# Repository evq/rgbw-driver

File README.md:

# RGBW LED Driver

A four channel LED driver board, designed for use with the Maple Mini
and other generic STM32F103 boards available on ebay and aliexpress. Shield
format, expecting PWM input from pins 8-11.

Shared on [OSH Park.](https://oshpark.com/shared_projects/hxdjCOfY)

## BOM

| Name           | Part                        |
|----------------|-----------------------------|
| Q1, Q2, Q3, Q4 | STN4NF03L N-Channel SOT-223 |
| R1, R2, R3, R4 | 0805 1M resistor            |
| R5, R6, R7, R8 | 0805 1k resistor            |

## Design notes
Polygon pours and thermal vias to help with any heat management issues.
Tested, board was produced by OSH Park. Designed to use the STN4NF03L
SOT-223 SMT N Channel MOSFET, but others could be substituted appropriately.

Designed to allow substitution with
right angle female pin header as surface mount to allow for mounting
of larger heatsink on the back. "LM2596 style" heatsinks (50mm x 25mm x 10mm) work
great.

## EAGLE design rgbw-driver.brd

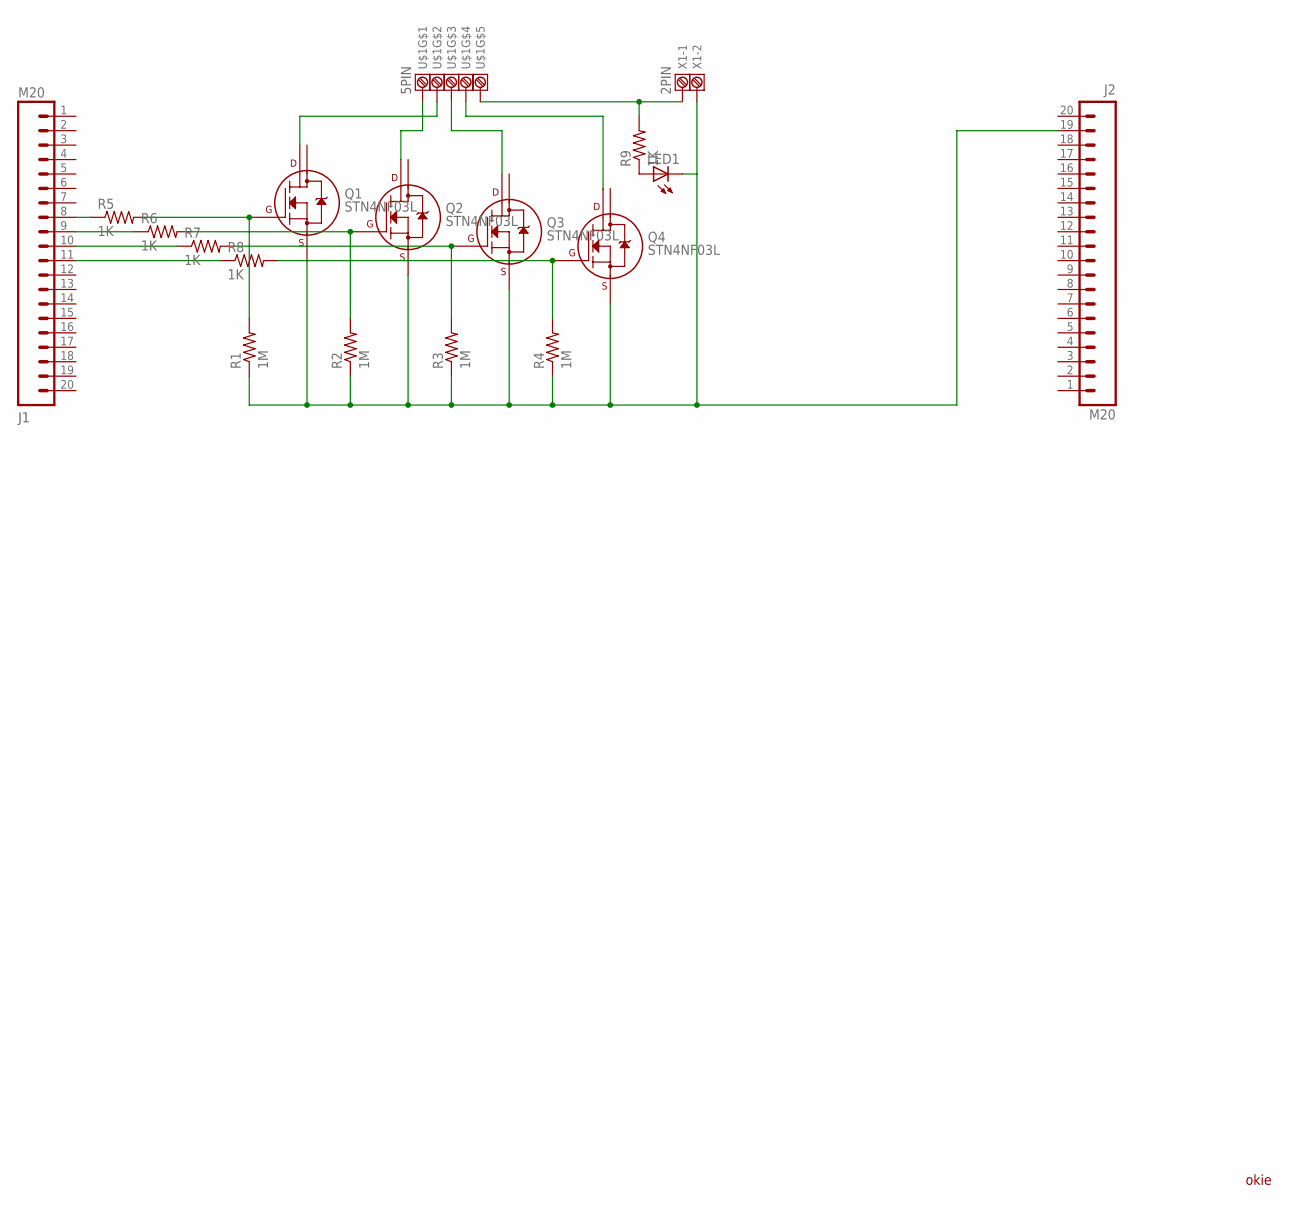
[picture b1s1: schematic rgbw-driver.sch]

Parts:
J1, J2: M20; 1X20
LED1: LEDCHIP-LED0805; CHIP-LED0805
Q1, Q2, Q3, Q4: STN4NF03L; SOT-223
R1, R2, R3, R4: 1M; R0805
R5, R6, R7, R8, R9: 1K; R0805
U$1: 5PIN
X1: 2PIN

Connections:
B: Q1.4 (D2), U$1.2
G: U$1.4
unnamed: J1.8, R5.1
unnamed: Q1.1 (G), R1.2, R5.2
unnamed: LED1.A, R9.1
unnamed: J2.19, LED1.C, Q1.3 (S), Q2.3 (S), Q3.3 (S), Q4.3 (S), R1.1, R2.1, R3.1, R4.1, X1.2
unnamed: Q4.1 (G), R4.2, R8.2
unnamed: R9.2, U$1.5, X1.1
unnamed: J1.9, R6.1
unnamed: J1.10, R7.1
unnamed: J1.11, R8.1
unnamed: Q2.1 (G), R2.2, R6.2
unnamed: Q3.1 (G), R3.2, R7.2
R: Q3.4 (D2), U$1.3
W: Q2.4 (D2), U$1.1

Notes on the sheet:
okie

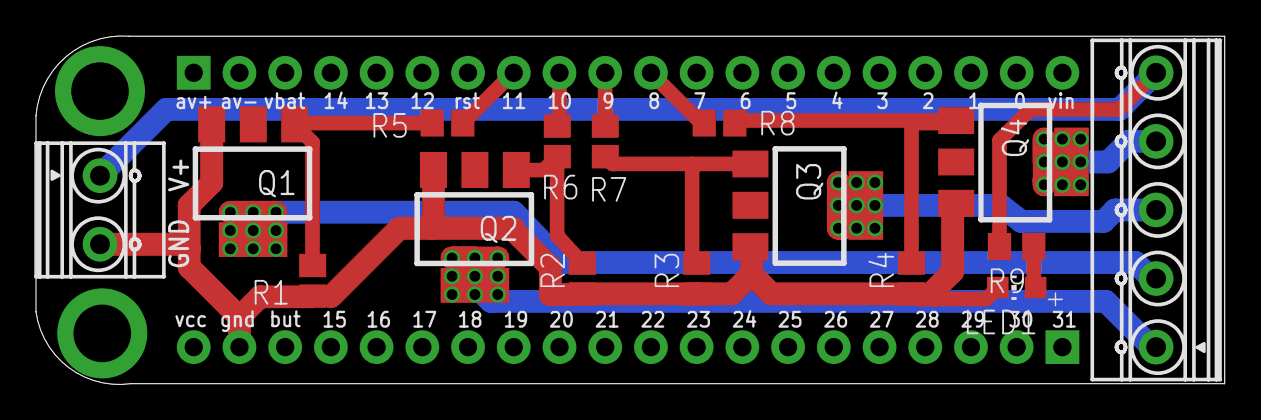
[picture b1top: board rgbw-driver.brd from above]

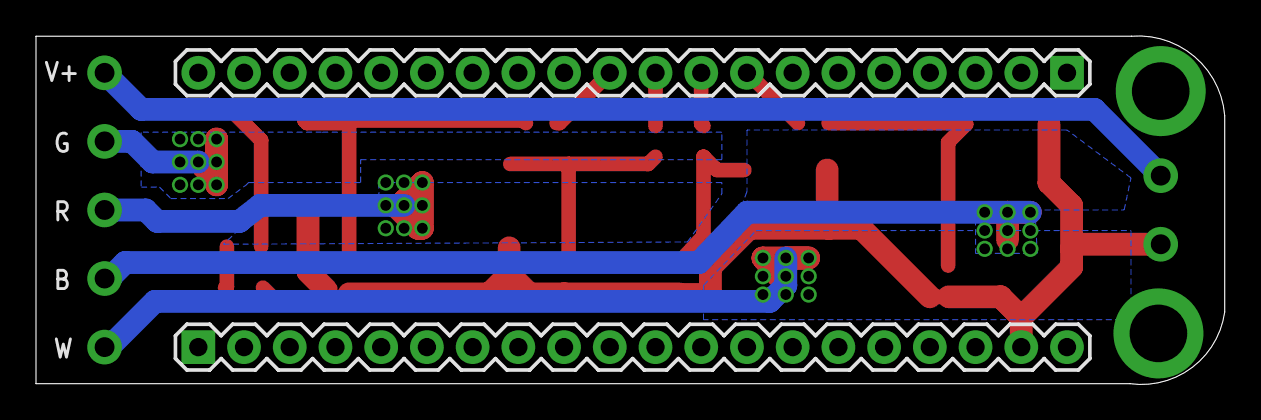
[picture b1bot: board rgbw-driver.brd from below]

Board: 2 copper layers, 66.0 x 19.4 mm, 18 parts (2 on the bottom side), 14 nets.

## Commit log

2015-04-09 Initial commit, sent to oshpark for fab
2015-04-13 RGBW traces now are polygonal pours for heat dissipation
2015-04-14 Minor schematic and silkscreen improvements
2015-06-10 Modifications to allow large heatsink for high current usage
2015-06-10 Added power indicator LED
